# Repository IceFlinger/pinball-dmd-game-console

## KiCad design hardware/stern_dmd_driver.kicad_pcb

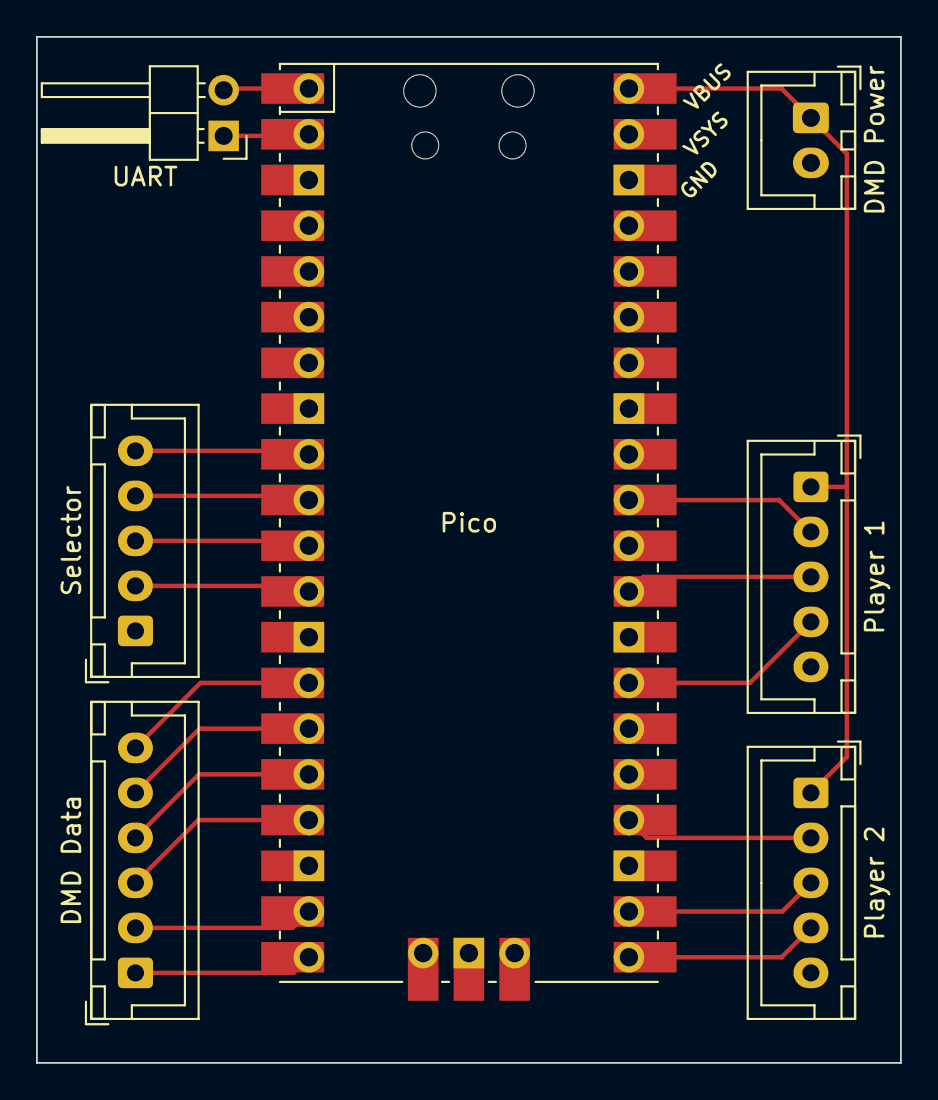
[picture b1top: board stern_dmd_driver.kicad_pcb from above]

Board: 2 copper layers, 48.0 x 57.0 mm, 7 parts (0 on the bottom side), 20 nets.

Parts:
DMD Data: Conn_DMD_Data; JST_XH_B6B-XH-A_1x06_P2.50mm_Vertical
DMD Power: Conn_DMD_Power; JST_XH_B2B-XH-A_1x02_P2.50mm_Vertical
Pico: Pico; RPi_Pico_SMD_TH
Player 1: Conn_Player1_Controller; JST_XH_B5B-XH-A_1x05_P2.50mm_Vertical
Player 2: Conn_Player2_Controller; JST_XH_B5B-XH-A_1x05_P2.50mm_Vertical
Selector: Conn_Selector; JST_XH_B5B-XH-A_1x05_P2.50mm_Vertical
UART: Conn_UART; PinHeader_1x02_P2.54mm_Horizontal

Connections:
+5V: DMD Power.1, Pico.40 (VBUS), Player 1.1, Player 2.1
GND: DMD Power.2, Pico.3 (GND), Pico.8 (GND), Pico.13 (GND), Pico.18 (GND), Pico.23 (GND), Pico.28 (GND), Pico.34 (GPIO28_ADC2), Pico.38 (GND), Player 1.5, Player 2.5, Selector.1
unnamed: Pico.1 (GPIO0), UART.2
unnamed: Pico.2 (GPIO1), UART.1
unnamed: Pico.9 (GPIO6), Selector.5
unnamed: Pico.10 (GPIO7), Selector.4
unnamed: Pico.11 (GPIO8), Selector.3
unnamed: Pico.12 (GPIO9), Selector.2
unnamed: DMD Data.6, Pico.14 (GPIO10)
unnamed: DMD Data.5, Pico.15 (GPIO11)
unnamed: DMD Data.4, Pico.16 (GPIO12)
unnamed: DMD Data.3, Pico.17 (GPIO13)
unnamed: DMD Data.2, Pico.19 (GPIO14)
unnamed: DMD Data.1, Pico.20 (GPIO15)
unnamed: Pico.21 (GPIO16), Player 2.4
unnamed: Pico.22 (GPIO17), Player 2.3
unnamed: Pico.24 (GPIO18), Player 2.2
unnamed: Pico.27 (GPIO21), Player 1.4
unnamed: Pico.29 (GPIO22), Player 1.3
unnamed: Pico.31 (GPIO26_ADC0), Player 1.2

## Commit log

2023-01-21 Add hardware files
2023-01-23 15 colors and multicore
